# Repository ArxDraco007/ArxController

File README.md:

# ArxController

## What is this?
A fully custom controller. Customizable according to your console. Firmware, 3D Models, and PCB design.

## Why did I make this?
Making your own controller is absolutely amazing! The process gives you a complete learning of wiring peripherals, Double LDO circuits, Battery charging protection, and the ESP32-WROOM module. This journey has been absolutely wonderful, and I would recommend this project for all intermediate PCB designers.

## PICTURES-

## Zine - 

## Build Instructions -
Soldering -
Start by applying flux to the pads on the footprint where you'll be soldering. Tin one of the pads with a small amount of solder, then carefully place your component onto the footprint. Touch your iron to the tinned pad to reflow it and tack the component in place, then let go with your tweezers once it's sitting right. Move to the opposite pad and solder it properly to the component. Finally, go back to your first pad and add a bit more solder to make sure you've got a solid joint.
Firmware - 
Plug in the ESP32-S3 via USB-C, select Board "ESP32S3 Dev Module" and the correct Port, hold BOOT while plugging in (or while pressing RESET) if it doesn't auto-detect, then click Upload to flash it, and finally press RESET or replug to run the new firmware.

## BOM

| Reference | Qty | Value | Footprint | Source | Buy Link |
|---|---|---|---|---|---|
| R2,R3 | 2 | 5.1k | Resistor_SMD:R_0603_1608Metric | Robu.in | [Link](https://robu.in/product/rc0603jr-075k1l-yageo-res-thick-film-0603-5-1k-ohm-5-0-1w1-10w-%C2%B1100ppm-c-pad-smd-t-r/) |
| R4 | 1 | 1.2k | Resistor_SMD:R_0603_1608Metric | LCSC | [Link](https://www.lcsc.com/search?q=0603+1.2K+ohm+resistor) |
| R5,R6,R7 | 3 | 1k | Resistor_SMD:R_0603_1608Metric | Robu.in | [Link](https://robu.in/product/1k-ohm-1-4w-0603-surface-mount-chip-resistor-pack-of-100/) |
| R8,R9 | 2 | 100R | Resistor_SMD:R_0603_1608Metric | LCSC | [Link](https://www.lcsc.com/search?q=0603+100R+1%25+resistor) |
| R10,R11,R12,R13,R14,R15,R16 | 7 | 100k | Resistor_SMD:R_0603_1608Metric | Robu.in | [Link](https://robu.in/product/100k-ohm-1-4w-0603-surface-mount-chip-resistor-pack-of-100/) |
| SW1 | 1 | EN (Tactile SMD) | Button_Switch_SMD:SW_SPST_TS-1088-xR020 | LCSC | [Link](https://www.lcsc.com/search?q=TS-1088) |
| SW2 | 1 | SW_PWR (Header) | Connector_PinSocket_2.54mm:PinSocket_1x03_P2.54mm_Vertical | Robu.in | [Link](https://robu.in/product/2-54mm-female-header-1x40-pin-strip/) |
| SW3 | 1 | BOOT (Tactile SMD) | custom_footprints:SW_SPST_TS-1088-xR020 | LCSC | [Link](https://www.lcsc.com/search?q=TS-1088) |
| SW4 | 1 | BTN_L (Shoulder switch) | custom_footprints:TS-1224VW | LCSC | [Link](https://www.lcsc.com/search?q=TS-1224VW) |
| SW5 | 1 | BTN_UP (Tactile 8mm) | custom_footprints:SW_PUSH_8mm_H5mm_custom | Robu.in | [Link](https://robu.in/product/6x6x5mm-tactile-push-button-switch-pack-of-10/) |
| SW6 | 1 | BTN_LEFT (Tactile 8mm) | custom_footprints:SW_PUSH_8mm_H5mm_custom | Robu.in | [Link](https://robu.in/product/6x6x5mm-tactile-push-button-switch-pack-of-10/) |
| SW7 | 1 | BTN_DOWN (Tactile 8mm) | custom_footprints:SW_PUSH_8mm_H5mm_custom | Robu.in | [Link](https://robu.in/product/6x6x5mm-tactile-push-button-switch-pack-of-10/) |
| SW8 | 1 | BTN_RIGHT (Tactile 8mm) | custom_footprints:SW_PUSH_8mm_H5mm_custom | Robu.in | [Link](https://robu.in/product/6x6x5mm-tactile-push-button-switch-pack-of-10/) |
| SW9 | 1 | BTN_START (Tactile 8mm) | custom_footprints:SW_PUSH_8mm_H5mm_custom | Robu.in | [Link](https://robu.in/product/6x6x5mm-tactile-push-button-switch-pack-of-10/) |
| SW10 | 1 | BTN_R (Shoulder switch) | custom_footprints:TS-1224VW | LCSC | [Link](https://www.lcsc.com/search?q=TS-1224VW) |
| SW11 | 1 | BTN_X (Tactile 8mm) | custom_footprints:SW_PUSH_8mm_H5mm_custom | Robu.in | [Link](https://robu.in/product/6x6x5mm-tactile-push-button-switch-pack-of-10/) |
| SW12 | 1 | BTN_A (Tactile 8mm) | custom_footprints:SW_PUSH_8mm_H5mm_custom | Robu.in | [Link](https://robu.in/product/6x6x5mm-tactile-push-button-switch-pack-of-10/) |
| SW13 | 1 | BTN_B (Tactile 8mm) | custom_footprints:SW_PUSH_8mm_H5mm_custom | Robu.in | [Link](https://robu.in/product/6x6x5mm-tactile-push-button-switch-pack-of-10/) |
| SW14 | 1 | BTN_Y (Tactile 8mm) | custom_footprints:SW_PUSH_8mm_H5mm_custom | Robu.in | [Link](https://robu.in/product/6x6x5mm-tactile-push-button-switch-pack-of-10/) |
| SW15 | 1 | BTN_SELECT (Tactile 8mm) | custom_footprints:SW_PUSH_8mm_H5mm_custom | Robu.in | [Link](https://robu.in/product/6x6x5mm-tactile-push-button-switch-pack-of-10/) |
| SW16 | 1 | BTN_SYS (Tactile 8mm) | custom_footprints:SW_PUSH_8mm_H5mm_custom | Robu.in | [Link](https://robu.in/product/6x6x5mm-tactile-push-button-switch-pack-of-10/) |
| TP1,TP3,TP5 | 3 | TestPoint | TestPoint:TestPoint_Pad_D2.0mm | Robu.in | [Link](https://robu.in/product/2mm-pin-female-header-1x40/) |
| TP4 | 1 | AMS_3V3 (TestPoint) | TestPoint:TestPoint_Pad_D2.0mm | Robu.in | [Link](https://robu.in/product/2mm-pin-female-header-1x40/) |
| U1 | 1 | ESP32-S3-WROOM-1-N16R8 | RF_Module:ESP32-S3-WROOM-1 | Robu.in | [Link](https://robu.in/product/espressif-esp32-s3-wroom-1-n16r8-module/) |
| U2 | 1 | MIC5219-3.3YM5 | Package_TO_SOT_SMD:SOT-23-5 | Robu.in | [Link](https://robu.in/product/mic5219-3-3ym5-tr-microchip-fixed-ldo-voltage-regulator-2-5v-to-12v-350mv-dropout-3-3vout-500maout-sot-23-5/) |
| U3 | 1 | TP4056-42-ESOP8 | Package_SO:SOIC-8-1EP_3.9x4.9mm_P1.27mm_EP2.41x3.3mm_ThermalVias | Robu.in | [Link](https://robu.in/product/tp4056-top-power-asic-4-2v-1a-standalone-linear-li-ion-battery-charger-with-thermal-regulation-sop8/) |
| U4 | 1 | DW01A | Package_TO_SOT_SMD:SOT-23-6 | Robu.in | [Link](https://robu.in/product/dw01a-4-3v-lithium-ion-lithium-polymer-battery-protection-ic-6pin-sot-23/) |
| U5 | 1 | AMS1117-3.3 | Package_TO_SOT_SMD:SOT-223-3_TabPin2 | Robu.in | [Link](https://robu.in/product/ams1117-3-3-slkor-800ma-70db120hz-fixed-3-3v-positive-electrode-18v-sot-223-voltage-regulators-linear-low-drop-out-ldo-regulators-rohs/) |
| U6 | 1 | PCM5102APWR | TSSOP-20 | Robu.in | [Link](https://robu.in/product/pcm5102apwr-texas-instruments-digital-to-analogue-converter-32-bit-384-ksps-i2s-3v-to-3-6v-tssop-20-pins/) |
| U7 | 1 | TPA2012D2 | QFN-16 | LCSC | [Link](https://www.lcsc.com/search?q=TPA2012D2) |
| U8 | 1 | ILI9341 TFT 2.4/2.8" Display Module | SPI 240x320 | LCSC | [Link](https://www.lcsc.com/search?q=ILI9341+2.8+SPI) |
| U9 | 1 | MAX17048G+T10 | SOT-23-6 (USOP-8) | LCSC | [Link](https://www.lcsc.com/search?q=MAX17048) |
| U10 | 1 | XC6220 LDO | SOT-23-5 | LCSC | [Link](https://www.lcsc.com/search?q=XC6220) |
| - | 1 | microSD Card Slot (Push-Push) | SMD microSD Socket | Robu.in | [Link](https://robu.in/product/micro-sd-card-tf-card-memory-card-socket-push-push-type-smd/) |
| - | 1 | USB-C Connector (16-pin) | USB_C_Receptacle_USB2.0_16P | Robu.in | [Link](https://robu.in/product/usb-type-c-16-pin-female-connector-smd/) |
| HW1-HW4   |   4 | M3 × 22mm Machine Screw | Mechanical:MountingHardware | element14 | [Link](https://in.element14.com/tr-fastenings/tr00008755-000/screw-flat-csk-head-sltd-m3-22mm/dp/4156380) |
| HW5-HW8   |   4 | M3 Hex Nut              | Mechanical:MountingHardware | FlyRobo | [Link](https://www.flyrobo.in/m3-ss-hex-nut-10pcs?srsltid=AfmBOopC71qpsOIubiWPyQa1-qcC8mzI4XCSzNWDzo-gBculU_eEorxn)              |
| FNIRSI HS-02 | 1 | Soldering | Soldering Iron | FNIRSI | [Link]("https://rees52.com/products/fnirsi-hs-01-intelligent-soldering-iron-hs-01-intelligent-temperature-controlled-soldering-iron-hs-01-automatic-sleep-mode-soldering-station-with-adjustable-temperature-for-diy-electronics-projects-black?variant=46392066769063")

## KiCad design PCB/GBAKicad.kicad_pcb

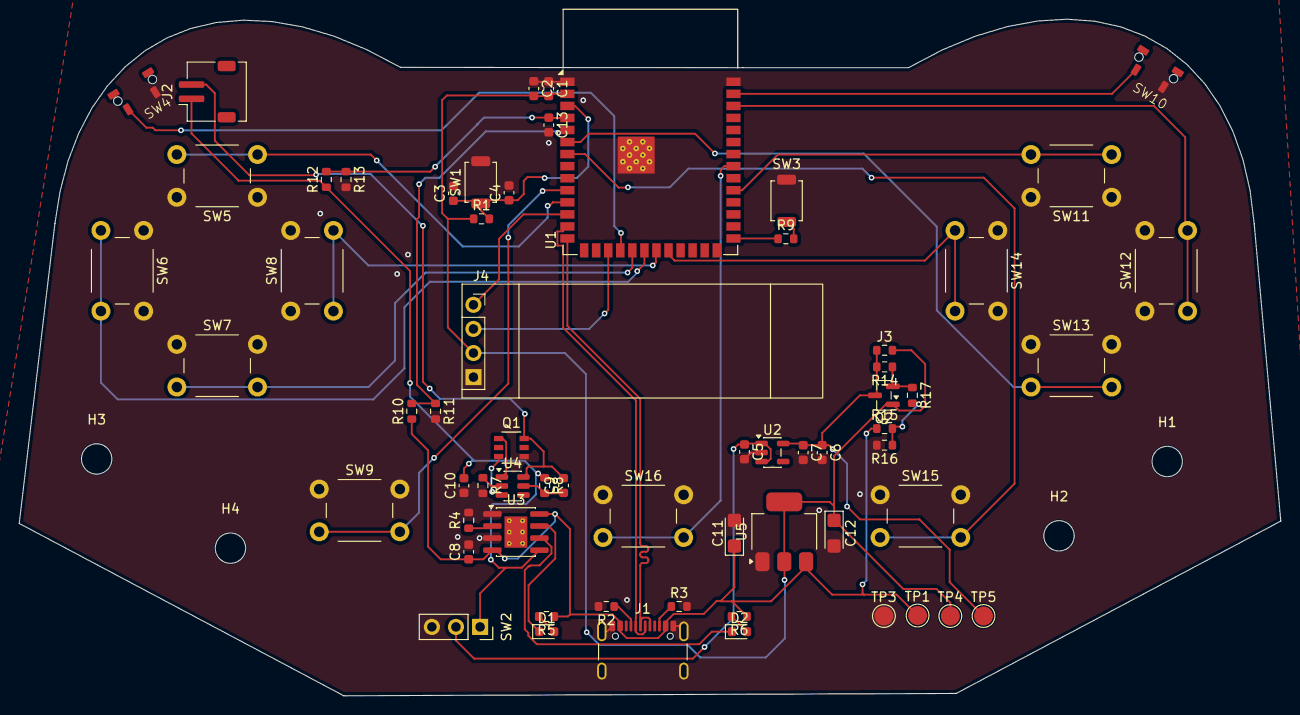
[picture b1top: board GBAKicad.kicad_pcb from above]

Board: 2 copper layers, 132.9 x 71.3 mm, 67 parts (0 on the bottom side), 42 nets.

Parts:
C1, C3, C13: 100nF; C_0603_1608Metric
C2: 22nF; C_0603_1608Metric
C4, C5, C6, C10: 10uF; C_0603_1608Metric
C7, C8, C9: 100uF; C_0603_1608Metric
C11: 10uF; CP_EIA-3216-18_Kemet-A
C12: 22uF; CP_EIA-3216-18_Kemet-A
D1: RED; LED_0603_1608Metric
D2: BLUE; LED_0603_1608Metric
H1, H2, H3, H4: MountingHole; MountingHole_3.2mm_M3
J1: USB_C_Receptacle_USB2.0_16P; USB_C_Receptacle_GCT_USB4105-xx-A_16P_TopMnt_Horizontal
J2: BATT_Conn; JST_ZH_S2B-ZR-SM4A-TF_1x02-1MP_P1.50mm_Horizontal
J3: Jumper; R_0603_1608Metric
J4: OLED_Conn; OLED128x32_1x04_P2.54mm_socket
Q1: SOT-23-6L_TCP
Q2: PMOS; SOT-23
R1, R17: 10k; R_0603_1608Metric
R2, R3: 5.1k; R_0603_1608Metric
R4: 1.2k; R_0603_1608Metric
R5, R6, R7: 1k; R_0603_1608Metric
R8, R9: 100R; R_0603_1608Metric
R10, R11, R12, R13, R14, R15, R16: 100k; R_0603_1608Metric
SW1: EN; SW_SPST_TS-1088-xR020
SW2: SW_PWR; PinSocket_1x03_P2.54mm_Vertical
SW3: BOOT; SW_SPST_TS-1088-xR020
SW4: BTN_L; TS-1224VW
SW5: BTN_UP; SW_PUSH_8mm_H5mm_custom
SW6: BTN_LEFT; SW_PUSH_8mm_H5mm_custom
SW7: BTN_DOWN; SW_PUSH_8mm_H5mm_custom
SW8: BTN_RIGHT; SW_PUSH_8mm_H5mm_custom
SW9: BTN_START; SW_PUSH_8mm_H5mm_custom
SW10: BTN_R; TS-1224VW
SW11: BTN_X; SW_PUSH_8mm_H5mm_custom
SW12: BTN_A; SW_PUSH_8mm_H5mm_custom
SW13: BTN_B; SW_PUSH_8mm_H5mm_custom
SW14: BTN_Y; SW_PUSH_8mm_H5mm_custom
SW15: BTN_SELECT; SW_PUSH_8mm_H5mm_custom
SW16: BTN_SYS; SW_PUSH_8mm_H5mm_custom
TP1, TP3, TP5: TestPoint; TestPoint_Pad_D2.0mm
TP4: AMS_3V3; TestPoint_Pad_D2.0mm
U1: ESP32-S3-WROOM-1
U2: MIC5219-3.3YM5; SOT-23-5
U3: TP4056-42-ESOP8; SOIC-8-1EP_3.9x4.9mm_P1.27mm_EP2.41x3.3mm_ThermalVias
U4: DW01A; SOT-23-6
U5: AMS1117-3.3; SOT-223-3_TabPin2

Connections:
+3V3: C1.2, C2.2, C12.1, J3.2 (B), J4.2, Q2.1 (D), R1.1, TP4.1 (1_1), U1.2 (3V3), U5.2 (VO)
+5V: C8.1, C11.1, J1.A4 (VBUS), J1.A9 (VBUS), J1.B4 (VBUS), J1.B9 (VBUS), R5.1, R6.1, R10.1, R15.1, TP1.1 (1_1), U3.4 (V_{CC}), U3.8 (CE), U5.3 (VI)
-BATT: C9.2, J2.2, Q1.3 (S2), U4.6 (GND)
BATT_CHECK: C13.1, R12.2, R13.1, U1.4 (IO4)
BOOT: R9.1, U1.27 (IO0)
BTN_A: SW12.2, U1.38 (IO2)
BTN_B: SW13.2, U1.6 (IO6)
BTN_DOWN: SW7.2, U1.19 (IO11)
BTN_L: SW4.2, U1.18 (IO10)
BTN_LEFT: SW6.2, U1.20 (IO12)
BTN_R: SW10.2, U1.39 (IO1)
BTN_RIGHT: SW8.2, U1.21 (IO13)
BTN_SELECT: SW15.2, U1.7 (IO7)
BTN_START: SW9.2, U1.10 (IO17)
BTN_SYS: SW16.2, U1.33 (IO40)
BTN_UP: SW5.2, U1.11 (IO18)
BTN_X: SW11.2, U1.31 (IO38)
BTN_Y: SW14.2, U1.22 (IO14)
CHRG_CHECK: R10.2, R11.1, U1.5 (IO5)
Data+: J1.A6 (D+), J1.B6 (D+), U1.14 (USB_D+)
Data-: J1.A7 (D-), J1.B7 (D-), U1.13 (USB_D-)
EN: C3.1, C4.1, R1.2, SW1.1, U1.3 (EN)
GND: C1.1, C2.1, C3.2, C4.2, C5.2, C6.2, C7.2, C8.2, C10.1, C11.2, C12.2, C13.2, J1.A1 (GND), J1.A12 (GND), J1.B1 (GND), J1.B12 (GND), J1.SH (SHIELD), J4.1, Q1.1 (S1), R2.2, R3.2, R4.2, R7.2, R11.2, R13.2, R16.2, SW1.2, SW2.3 (C), SW3.2, SW4.1, SW5.1, SW6.1, SW7.1, SW8.1, SW9.1, SW10.1, SW11.1, SW12.1, SW13.1, SW14.1, SW15.1, SW16.1, TP3.1 (1_1), U1.1 (GND), U1.40 (GND), U1.41 (GND), U2.2 (GND), U3.1 (TEMP), U3.3 (GND), U5.1 (GND)
unnamed: D1.2 (A), R5.2
unnamed: D1.1 (K), U3.7 (~CHRG)
unnamed: D2.2 (A), R6.2
unnamed: D2.1 (K), U3.6 (~STDBY)
unnamed: J1.A5 (CC1), R2.1
unnamed: J1.B5 (CC2), R3.1
unnamed: C6.1, C7.1, J3.1 (A), Q2.3 (S), R14.2, TP5.1 (1_1), U2.5 (OUT)
unnamed: Q1.6 (G1), U4.3 (OC)
unnamed: Q1.4 (G2), U4.1 (OD)
unnamed: Q2.2 (G), R14.1, R17.1
unnamed: R9.2, SW3.1
unnamed: R15.2, R16.1, R17.2
unnamed: C5.1, SW2.2 (B), U2.1 (IN), U2.3 (EN)
unnamed: R4.1, U3.2 (PROG)
unnamed: R7.1, U4.2 (CS)
unnamed: C9.1, R8.2, U4.5 (VCC)
OLED_SCK: J4.3, U1.17 (IO9)
OLED_SDA: J4.4, U1.12 (IO8)
OUT+: C10.2, J2.1, R8.1, R12.1, SW2.1 (A), U3.5 (BAT)

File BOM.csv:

"Reference","Qty","Value","Footprint","Source","Buy Link (India)"
"R2,R3","2","5.1k","Resistor_SMD:R_0603_1608Metric","Robu.in","https://robu.in/product/rc0603jr-075k1l-yageo-res-thick-film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"
"R4","1","1.2k","Resistor_SMD:R_0603_1608Metric","LCSC","https://www.lcsc.com/search?q=0603+1.2K+ohm+resistor"
"R5,R6,R7","3","1k","Resistor_SMD:R_0603_1608Metric","Robu.in","https://robu.in/product/1k-ohm-1-4w-0603-surface-mount-chip-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"
"R8,R9","2","100R","Resistor_SMD:R_0603_1608Metric","LCSC","https://www.lcsc.com/search?q=0603+100R+1%25+resistor"
"R10,R11,R12,R13,R14,R15,R16","7","100k","Resistor_SMD:R_0603_1608Metric","Robu.in","https://robu.in/product/100k-ohm-1-4w-0603-surface-mount-chi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"
"SW1","1","EN (Tactile SMD)","Button_Switch_SMD:SW_SPST_TS-1088-xR020","LCSC","https://www.lcsc.com/search?q=TS-1088"
"SW2","1","SW_PWR (Header)","Connector_PinSocket_2.54mm:PinSocket_1x03_P2.54mm_Vertical","Robu.in","https://robu.in/product/2-54mm-female-header-1x40-pin-strip/"
"SW3","1","BOOT (Tactile SMD)","custom_footprints:SW_SPST_TS-1088-xR020","LCSC","https://www.lcsc.com/search?q=TS-1088"
"SW4","1","BTN_L (Shoulder switch)","custom_footprints:TS-1224VW","LCSC","https://www.lcsc.com/search?q=TS-1224VW"
"SW5","1","BTN_UP (Tactile 8mm)","custom_footprints:SW_PUSH_8mm_H5mm_custom","Robu.in","https://robu.in/product/6x6x5mm-tactile-push-button-switch-p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"
"SW6","1","BTN_LEFT (Tactile 8mm)","custom_footprints:SW_PUSH_8mm_H5mm_custom","Robu.in","https://robu.in/product/6x6x5mm-tactile-push-button-switch-p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"
"SW7","1","BTN_DOWN (Tactile 8mm)","custom_footprints:SW_PUSH_8mm_H5mm_custom","Robu.in","https://robu.in/product/6x6x5mm-tactile-push-button-switch-p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"
"SW8","1","BTN_RIGHT (Tactile 8mm)","custom_footprints:SW_PUSH_8mm_H5mm_custom","Robu.in","https://robu.in/product/6x6x5mm-tactile-push-button-switch-p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"
"SW9","1","BTN_START (Tactile 8mm)","custom_footprints:SW_PUSH_8mm_H5mm_custom","Robu.in","https://robu.in/product/6x6x5mm-tactile-push-button-switch-p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"
"SW10","1","BTN_R (Shoulder switch)","custom_footprints:TS-1224VW","LCSC","https://www.lcsc.com/search?q=TS-1224VW"
"SW11","1","BTN_X (Tactile 8mm)","custom_footprints:SW_PUSH_8mm_H5mm_custom","Robu.in","https://robu.in/product/6x6x5mm-tactile-push-button-switch-p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"
"SW12","1","BTN_A (Tactile 8mm)","custom_footprints:SW_PUSH_8mm_H5mm_custom","Robu.in","https://robu.in/product/6x6x5mm-tactile-push-button-switch-p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"
"SW13","1","BTN_B (Tactile 8mm)","custom_footprints:SW_PUSH_8mm_H5mm_custom","Robu.in","https://robu.in/product/6x6x5mm-tactile-push-button-switch-p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"
"SW14","1","BTN_Y (Tactile 8mm)","custom_footprints:SW_PUSH_8mm_H5mm_custom","Robu.in","https://robu.in/product/6x6x5mm-tactile-push-button-switch-p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"
"SW15","1","BTN_SELECT (Tactile 8mm)","custom_footprints:SW_PUSH_8mm_H5mm_custom","Robu.in","https://robu.in/product/6x6x5mm-tactile-push-button-switch-p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"
"SW16","1","BTN_SYS (Tactile 8mm)","custom_footprints:SW_PUSH_8mm_H5mm_custom","Robu.in","https://robu.in/product/6x6x5mm-tactile-push-button-switch-p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"
"TP1,TP3,TP5","3","TestPoint","TestPoint:TestPoint_Pad_D2.0mm","Robu.in","https://robu.in/product/2mm-pin-female-header-1x40/"
"TP4","1","AMS_3V3 (TestPoint)","TestPoint:TestPoint_Pad_D2.0mm","Robu.in","https://robu.in/product/2mm-pin-female-header-1x40/"
"U1","1","ESP32-S3-WROOM-1-N16R8","RF_Module:ESP32-S3-WROOM-1","Robu.in","https://robu.in/product/espressif-esp32-s3-wroom-1-n16r8-module/"
"U2","1","MIC5219-3.3YM5","Package_TO_SOT_SMD:SOT-23-5","Robu.in","https://robu.in/product/mic5219-3-3ym5-tr-microchip-fixed-ld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"
"U3","1","TP4056-42-ESOP8","Package_SO:SOIC-8-1EP_3.9x4.9mm_P1.27mm_EP2.41x3.3mm_ThermalVias","Robu.in","https://robu.in/product/tp4056-top-power-asic-4-2v-1a-standa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"
"U4","1","DW01A","Package_TO_SOT_SMD:SOT-23-6","Robu.in","https://robu.in/product/dw01a-4-3v-lithium-ion-lithium-polym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"
"U5","1","AMS1117-3.3","Package_TO_SOT_SMD:SOT-223-3_TabPin2","Robu.in","https://robu.in/product/ams1117-3-3-slkor-800ma-70db120hz-fi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"
"U6","1","PCM5102APWR","TSSOP-20","Robu.in","https://robu.in/product/pcm5102apwr-texas-instruments-digita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"
"U7","1","TPA2012D2","QFN-16","LCSC","https://www.lcsc.com/search?q=TPA2012D2"
"U8","1","ILI9341 TFT 2.4 Display Module","SPI 240x320","LCSC","https://www.lcsc.com/search?q=ILI9341+2.8+SPI"
"U9","1","MAX17048G+T10","SOT-23-6 (USOP-8)","LCSC","https://www.lcsc.com/search?q=MAX17048"
"U10","1","XC6220 LDO","SOT-23-5","LCSC","https://www.lcsc.com/search?q=XC6220"
"MicroSD","1","microSD Card Slot (Push-Push)","SMD microSD Socket","Robu.in","https://robu.in/product/micro-sd-card-tf-card-memory-card-so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"
"USB Connector Pin","1","USB-C Connector (16-pin)","USB_C_Receptacle_USB2.0_16P","Robu.in","https://robu.in/product/usb-type-c-16-pin-female-connector-smd/"
"HW1-HW4","4","M3 × 22mm Machine Screw","Mechanical:MountingHardware","element14","https://in.element14.com/tr-fastenings/tr00008755-000/screw-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"
"HW5-HW8","4","M3 Hex Nut","Mechanical:MountingHardware","FlyRobo","https://www.flyrobo.in/m3-ss-hex-nut-10pcs?srsltid=AfmBOopC7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"

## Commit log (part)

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2026-06-11 transfer
2026-06-11 removing redundance
2026-06-13 zine!!
2026-06-17 CAD files
2026-06-17 Update zine image in README
2026-06-25 Add FNIRSI HS-02 soldering iron to BOM
